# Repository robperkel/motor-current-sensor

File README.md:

# Hall Effect Current Sensor

## Disclaimer

**Build and use this circuit at your own risk.** This circuit has not been tested to determine the maximum current possible (without the PCB igniting/melting) or the maximum input voltage on the current sensing side.

If high voltages are applied to the current sense side, the PCB may become a shock hazard. While the current sense side is isolated from the outputs - arcing, debris/dirt, assembly errors or design defects could cause it to jump to the output side. **Excerise extreme caution when working with hazardous voltages.**

## Tools and Components

- [KiCad 8.0.1](https://www.kicad.org/)  
- [FreeCad](https://www.freecad.org/)  

## Measuring the Current

The objective of this circuit is to measure current in an isolated fashion. For me (the author), this is to characterize current flow in a Stepper Motor, however this design can be used in other applications. To perform this task, a [Hall Effect sensor (ACS37030) by Allegro Microsystems](https://www.allegromicro.com/en/products/sense/current-sensor-ics/zero-to-fifty-amp-integrated-conductor-sensor-ics/acs37030-2) is used. 

**Note**: The ACS37030 has multiple different current ranges available, but at the time of this readme, only the 40A part is available. 

**Caution: While the sensor can measure high currents (20A/40A/65A), the PCB is NOT tested or characterized for this.** Use of high copper weight PCB material is likely required.  

This part was choosen due to it's high BW range (DC to 5 MHz), which is uncommon for these ICs. Since the current-side circuit is isolated, it is possible to measure current with high common voltages on the current sense side.

## Driving the Cable

To drive the cable to the oscilloscope, an [MCP633 Operational Amplifier by Microchip](https://www.microchip.com/en-us/product/MCP633) is implemented as a non-inverting amplifier with a gain of 3. The MCP633 has a Gain Bandwidth Product (GBWP) of 24 MHz, which provides enough BW to run at a gain of 3 without limiting the circuit performance. In this configuration, the output of this circuit is 99 mV/A. 

**Note**: The gain of the circuit can be changed by modifying the ratio of R1/R4 in the schematic. 

Power for this board is supplied over USB-C (at 5V). The ACS37030 is designed for 3V operation, so a simple Zener shunt regulator is used to regulate the power supply for the sensor, while the operational amplifier uses the raw USB bus voltage.

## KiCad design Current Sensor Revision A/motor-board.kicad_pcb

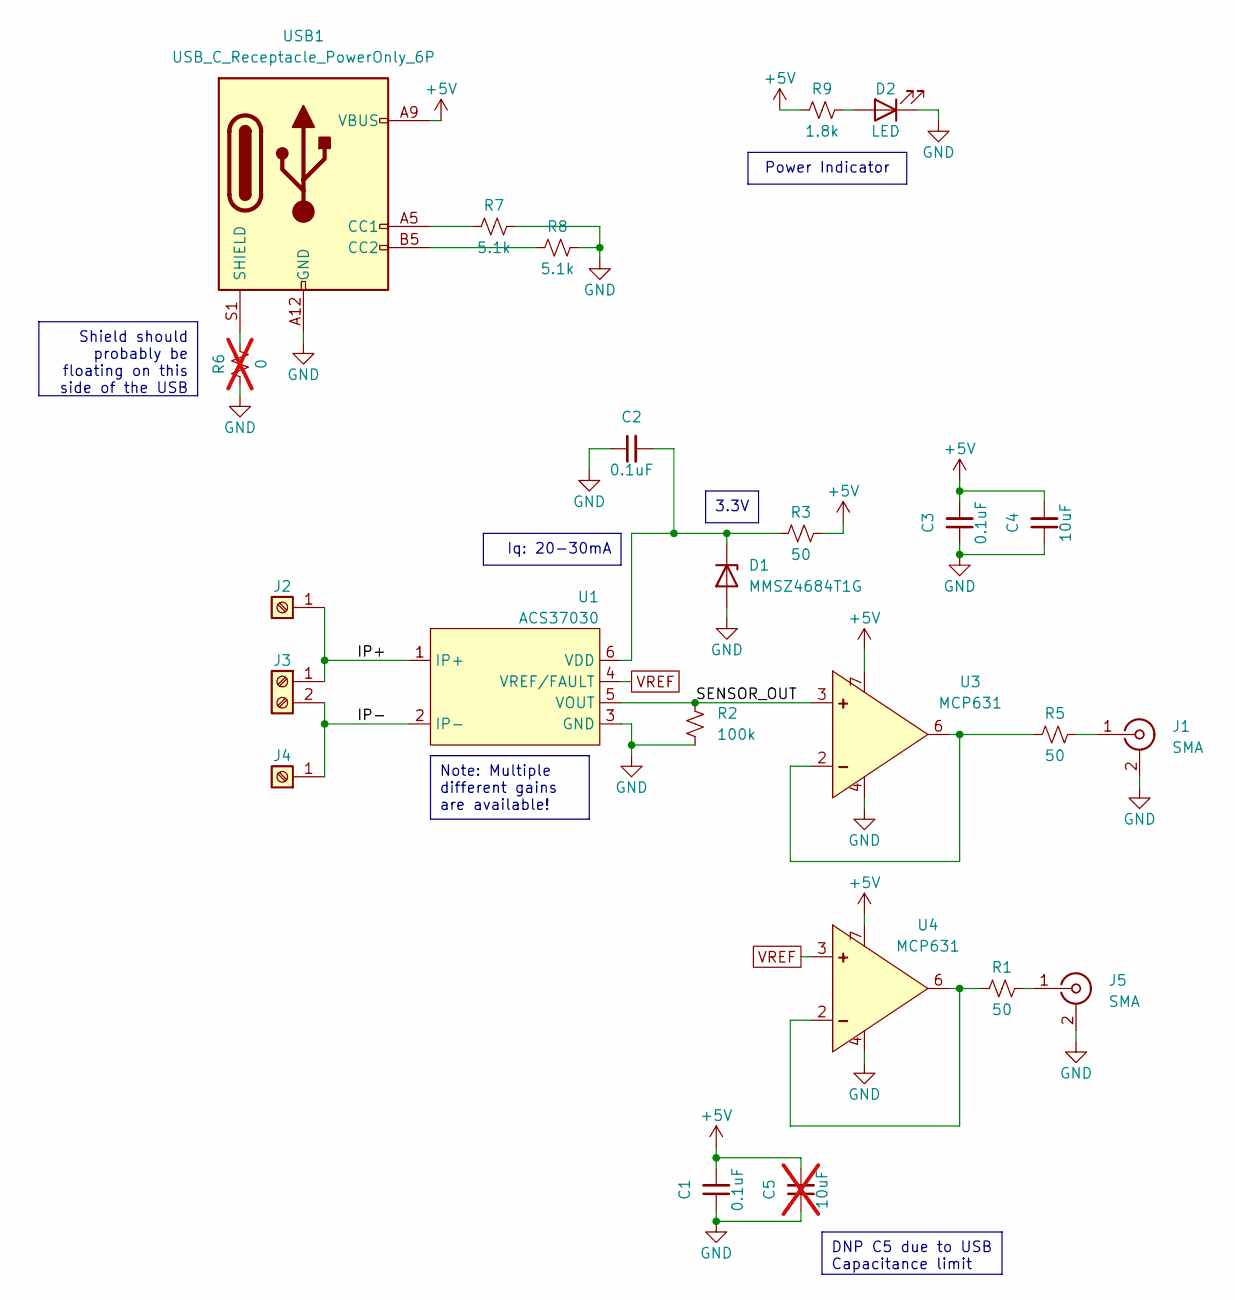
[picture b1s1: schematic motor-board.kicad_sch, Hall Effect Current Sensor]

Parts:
C1, C2, C3: 0.1uF; C_0805_2012Metric_Pad1.18x1.45mm_HandSolder
C4: 10uF; C_0805_2012Metric_Pad1.18x1.45mm_HandSolder
C5: 10uF; C_0805_2012Metric_Pad1.18x1.45mm_HandSolder; not fitted
D1: MMSZ4684T1G; SOT-123
D2: LED; LED 0805
J1, J5: SMA; CONSMA002-L-G
J2, J4: 74650094R
J3: Screw_Terminal_01x02; 6PCV-02-007
R1, R3, R5: 50; R_1206_3216Metric_Pad1.30x1.75mm_HandSolder
R2: 100k; R_0805_2012Metric_Pad1.20x1.40mm_HandSolder
R6: 0; R_0805_2012Metric_Pad1.20x1.40mm_HandSolder; not fitted
R7, R8: 5.1k; R_0805_2012Metric_Pad1.20x1.40mm_HandSolder
R9: 1.8k; R_0805_2012Metric_Pad1.20x1.40mm_HandSolder
U1: ACS37030; Custom 6-pin SOIC (only for ACS37030ACS37032)
U3, U4: MCP631; SOIC-8
USB1: USB_C_Receptacle_PowerOnly_6P; 10164359-00011LF

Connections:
+5V: C1.2, C3.2, C4.2, C5.2, R3.2, R9.1, U3.7 (VDD), U4.7 (VDD), USB1.A9 (VBUS), USB1.B9 (VBUS)
/IP+: J2.1, J3.1, U1.1 (IP+)
/IP-: J3.2, J4.1, U1.2 (IP-)
/SENSOR_OUT: R2.1, U1.5 (VOUT), U3.3 (IN+)
GND: C1.1, C2.1, C3.1, C4.1, C5.1, D1.2 (A), D2.1 (K), J1.2 (Ext), J5.2 (Ext), R2.2, R6.1, R7.2, R8.2, U1.3 (GND), U3.4 (VSS), U4.4 (VSS), USB1.A12 (GND), USB1.B12 (GND)
unnamed: C2.2, D1.1 (K), R3.1, U1.6 (VDD)
unnamed: D2.2 (A), R9.2
unnamed: J1.1 (In), R5.2
unnamed: J5.1 (In), R1.2
unnamed: R5.1, U3.2 (IN-), U3.6 (VOUT)
unnamed: R1.1, U4.2 (IN-), U4.6 (VOUT)
unnamed: R7.1, USB1.A5 (CC1)
unnamed: R8.1, USB1.B5 (CC2)
unnamed: R6.2, USB1.S1 (SHIELD)
VREF: U1.4 (VREF/FAULT), U4.3 (IN+)

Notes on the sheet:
Power Indicator
DNP C5 due to USB Capacitance limit
3.3V
Note: Multiple different gains are available!
Iq: 20-30mA
Shield should probably be floating on this side of the USB

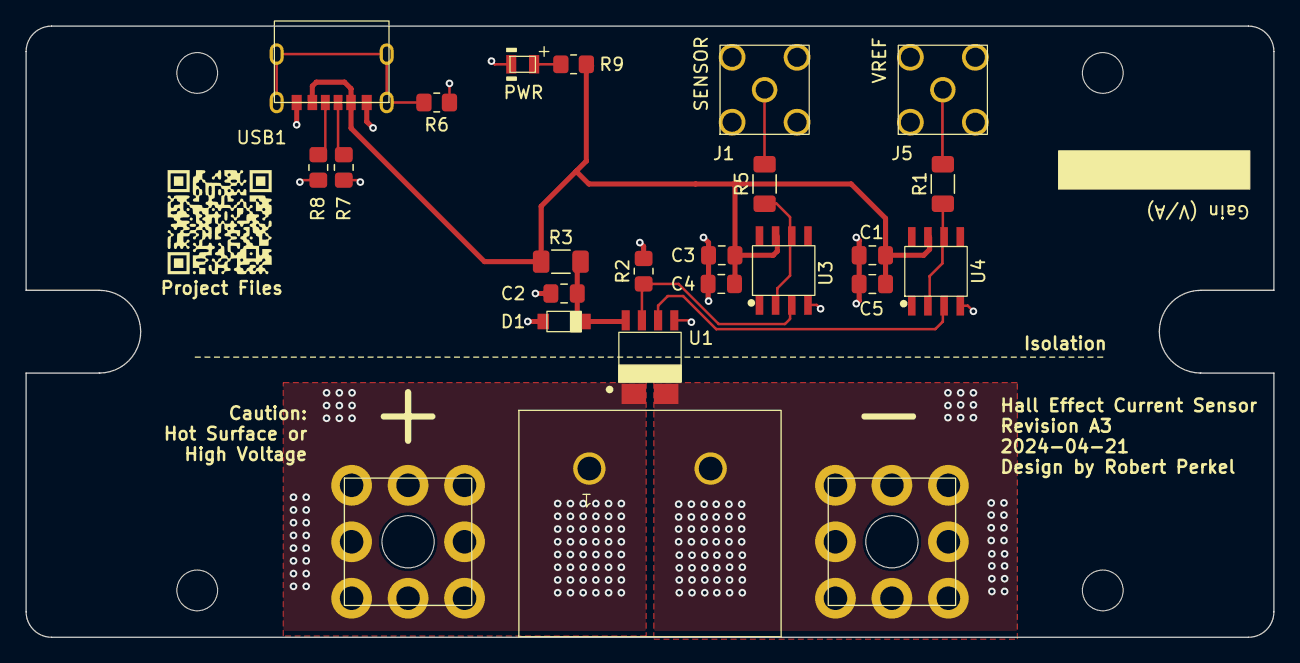
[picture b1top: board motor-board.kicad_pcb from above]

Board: 2 copper layers, 98.0 x 48.0 mm, 24 parts (0 on the bottom side), 15 nets.

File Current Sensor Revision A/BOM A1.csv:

"Reference","Value","Footprint","Qty","DNP"
"C1,C2,C3","0.1uF","Capacitor_SMD:C_0805_2012Metric_Pad1.18x1.45mm_HandSolder","3",""
"C4","10uF","Capacitor_SMD:C_0805_2012Metric_Pad1.18x1.45mm_HandSolder","1",""
"C5","10uF","Capacitor_SMD:C_0805_2012Metric_Pad1.18x1.45mm_HandSolder","1","DNP"
"D1","MMSZ4684T1G","StandardPackages_Custom:SOT-123","1",""
"D2","LED","StandardPackages_Custom:LED 0805","1",""
"J1,J5","SMA","Current Sensor PCB Library:CONSMA002-L-G","2",""
"J2,J4","74650094R","Current Sensor PCB Library:74650094R","2",""
"J3","Screw_Terminal_01x02","Current Sensor PCB Library:6PCV-02-007","1",""
"R1,R3,R5","50","Resistor_SMD:R_1206_3216Metric_Pad1.30x1.75mm_HandSolder","3",""
"R2","100k","Resistor_SMD:R_0805_2012Metric_Pad1.20x1.40mm_HandSolder","1",""
"R6","0","Resistor_SMD:R_0805_2012Metric_Pad1.20x1.40mm_HandSolder","1","DNP"
"R7,R8","5.1k","Resistor_SMD:R_0805_2012Metric_Pad1.20x1.40mm_HandSolder","2",""
"R9","1.8k","Resistor_SMD:R_0805_2012Metric_Pad1.20x1.40mm_HandSolder","1",""
"U1","ACS37030","Current Sensor PCB Library:Custom 6-pin SOIC (only for ACS37030ACS37032)","1",""
"U3,U4","MCP631","StandardPackages_Custom:SOIC-8","2",""
"USB1","USB_C_Receptacle_PowerOnly_6P","Current Sensor PCB Library:10164359-00011LF","1",""

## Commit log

2024-04-08 PCB Files
2024-04-08 Renamed KiCad files to be consistent
2024-04-08 Filled in README
2024-04-22 Added A2/A3 PCB files and 3D Board Render
